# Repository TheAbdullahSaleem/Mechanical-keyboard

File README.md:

# Mechanical KEEB!!! 
This is a keyboard completely made by me 

## HOW THIS WAS MADE
I made it from scratch compltely scratch and followed the keeb.hackclub guide for it

## How to install:
It is not installable how ever you can see the 3d model at https://cad.onshape.com/documents/bb4cb905776d924b12e08e8f/w/9ffe8c12da04f62d852a73e0/e/dd87c740e253aa3d1df2d833?renderMode=0&uiState=6ac13d8ddb4687ee592e63fd
or just clone this repo

## FEEDBACK:
Your feedbacks are very valuable for us , message me on slack my handle is @Mewton (I know its funny it is like cat plus newton)

## AI DISCLOSURE
I used ai for some testing and clarity cuz it was my first project like this

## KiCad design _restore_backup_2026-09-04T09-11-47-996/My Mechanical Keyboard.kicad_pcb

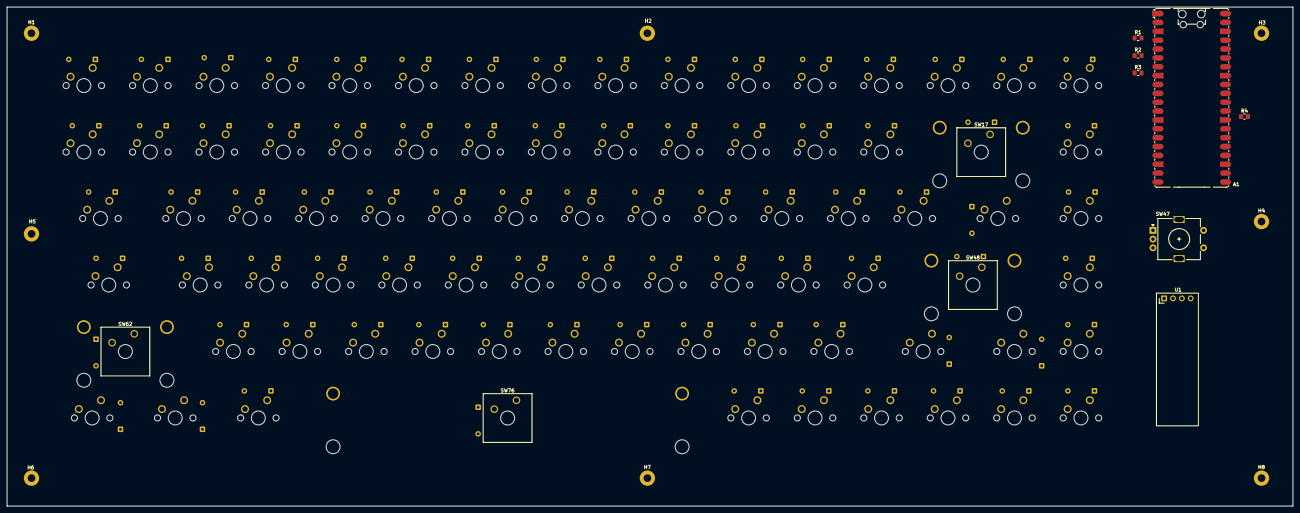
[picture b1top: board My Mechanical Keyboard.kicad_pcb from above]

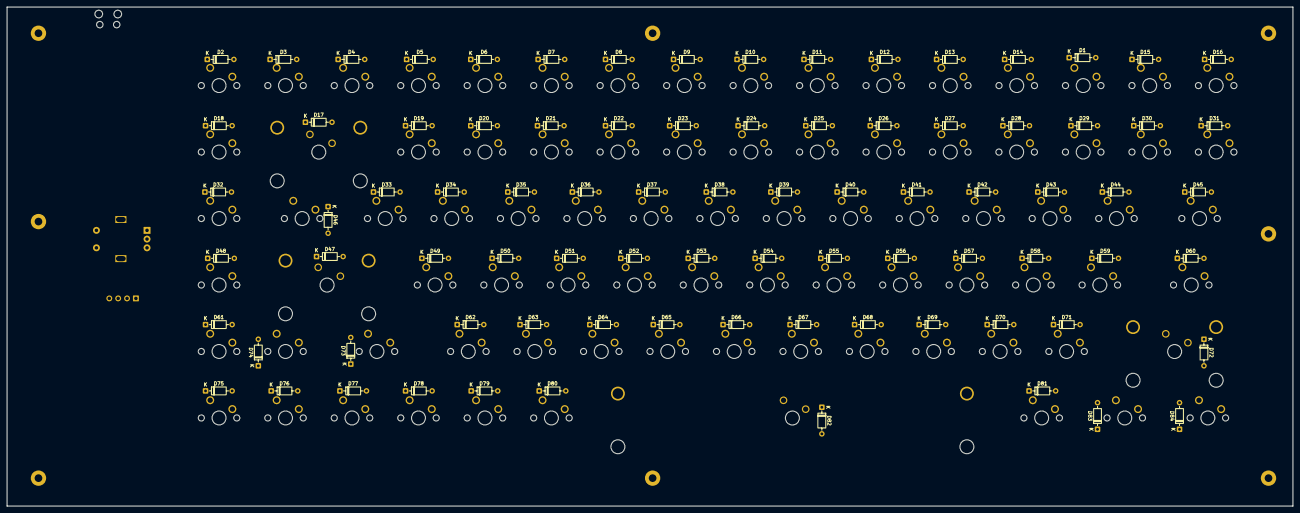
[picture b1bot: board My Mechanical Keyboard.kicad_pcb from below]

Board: 2 copper layers, 368.5 x 143.0 mm, 187 parts (84 on the bottom side), 111 nets, no tracks yet.

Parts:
A1: RaspberryPi_Pico; RaspberryPi_Pico_Common_SMD
D1, D2, D3, D4, D5, D6, D7, D8, D9, D10, D11, D12, D13, D14, D15, D16, D17, D18, D19, D20, D21, D22, D23, D24, D25, D26, D27, D28, D29, D30, D31, D32, D33, D34, D35, D36, D37, D38, D39, D40, D41, D42, D43, D44, D45, D46, D47, D48, D49, D50, D51, D52, D53, D54, D55, D56, D57, D58, D59, D60, D61, D62, D63, D64, D65, D66, D67, D68, D69, D70, D71, D72, D73, D74, D75, D76, D77, D78, D79, D80, D81, D82, D83, D84: 1N4148; D_DO-35_SOD27_P7.62mm_Horizontal
H1, H2, H3, H4, H5, H6, H7, H8: MountingHole; MountingHole_2.2mm_M2_Pad
R1, R2: 4.7k; R_0805_2012Metric_Pad1.20x1.40mm_HandSolder
R3, R4: 5.1k; R_0805_2012Metric_Pad1.20x1.40mm_HandSolder
S1: MX_stab; STAB_MX_P_2u
S2, S3: MX_stab; STAB_MX_P_2.25u
S4: MX_stab; STAB_MX_P_6.25u
SW1, SW2, SW3, SW4, SW5, SW6, SW7, SW8, SW9, SW10, SW11, SW12, SW13, SW14, SW15, SW16, SW18, SW19, SW20, SW21, SW22, SW23, SW24, SW25, SW26, SW27, SW28, SW29, SW30, SW31, SW33, SW34, SW35, SW36, SW37, SW38, SW39, SW40, SW41, SW42, SW43, SW44, SW46, SW50, SW51, SW52, SW53, SW54, SW55, SW56, SW57, SW58, SW59, SW60, SW61, SW63, SW64, SW65, SW66, SW67, SW68, SW69, SW70, SW71, SW72, SW74, SW75, SW80, SW81, SW82, SW83, SW84, SW85: SW_Push; SW_MX_1u
SW17: SW_Push; SW_Cherry_MX_2.00u_Plate
SW32, SW45: SW_Push; SW_MX_1.5u
SW47: RotaryEncoder_Switch; RotaryEncoder_Alps_EC11E-Switch_Vertical_H20mm
SW48, SW62: SW_Push; SW_Cherry_MX_2.25u_Plate
SW49, SW73: SW_Push; SW_MX_1.75u
SW76: SW_Push; SW_Cherry_MX_6.25u_Plate
SW77, SW78, SW79: SW_Push; SW_MX_1.25u
U1: ER_OLEDM0.91_1x-I2C

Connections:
+3V3: A1.36 (3V3), R1.2, R2.1, U1.2 (VCC)
/Col 1: A1.15 (GPIO11), SW1.1, SW18.1, SW32.1, SW49.1, SW62.1, SW77.1
/Col 2: A1.16 (GPIO12), SW2.1, SW19.1, SW33.1, SW50.1, SW63.1, SW78.1
/Col 3: A1.17 (GPIO13), SW3.1, SW20.1, SW34.1, SW51.1, SW64.1, SW79.1
/Col 4: A1.19 (GPIO14), SW4.1, SW21.1, SW35.1, SW52.1, SW65.1, SW76.1
/Col 5: A1.20 (GPIO15), SW5.1, SW22.1, SW36.1, SW53.1, SW66.1, SW67.1
/Col 6: A1.21 (GPIO16), SW6.1, SW23.1, SW37.1, SW54.1, SW55.1, SW68.1
/Col 7: A1.22 (GPIO17), SW7.1, SW24.1, SW38.1, SW39.1, SW56.1, SW69.1
/Col 8: A1.24 (GPIO18), SW8.1, SW25.1, SW26.1, SW40.1, SW57.1, SW70.1
/Col 9: A1.25 (GPIO19), SW9.1, SW27.1, SW41.1, SW58.1, SW71.1, SW80.1
/Col 10: A1.26 (GPIO20), SW10.1, SW28.1, SW42.1, SW59.1, SW72.1, SW81.1
/Col 11: A1.27 (GPIO21), SW11.1, SW29.1, SW43.1, SW60.1, SW73.1, SW82.1
/Col 12: A1.29 (GPIO22), SW12.1, SW30.1, SW44.1, SW48.1, SW74.1, SW83.1
/Col 13: A1.31 (GPIO26_ADC0), SW13.1, SW14.1, SW17.1, SW45.1, SW75.1, SW84.1
/Col 14: A1.32 (GPIO27_ADC1), SW15.1, SW16.1, SW31.1, SW46.1, SW61.1, SW85.1
/ENC_A: A1.1 (GPIO0), SW47.A
/ENC_B: A1.2 (GPIO1), SW47.B
/ENC_SW: A1.4 (GPIO2), SW47.S1
/Row 1: A1.7 (GPIO5), D1.2 (A), D3.2 (A), D5.2 (A), D6.2 (A), D7.2 (A), D8.2 (A), D9.2 (A), D10.2 (A), D11.2 (A), D12.2 (A), D13.2 (A), D14.2 (A), D15.2 (A), D16.2 (A)
/Row 2: A1.9 (GPIO6), D2.2 (A), D4.2 (A), D19.2 (A), D20.2 (A), D21.2 (A), D22.2 (A), D24.2 (A), D25.2 (A), D26.2 (A), D27.2 (A), D28.2 (A), D29.2 (A), D30.2 (A), D31.2 (A)
/Row 3: A1.10 (GPIO7), D17.2 (A), D18.2 (A), D23.2 (A), D33.2 (A), D34.2 (A), D35.2 (A), D36.2 (A), D39.2 (A), D40.2 (A), D41.2 (A), D42.2 (A), D43.2 (A), D44.2 (A), D45.2 (A)
/Row 4: A1.11 (GPIO8), D32.2 (A), D37.2 (A), D38.2 (A), D46.2 (A), D47.2 (A), D49.2 (A), D50.2 (A), D51.2 (A), D55.2 (A), D56.2 (A), D57.2 (A), D58.2 (A), D59.2 (A), D60.2 (A)
/Row 5: A1.12 (GPIO9), D48.2 (A), D52.2 (A), D53.2 (A), D54.2 (A), D61.2 (A), D62.2 (A), D63.2 (A), D68.2 (A), D69.2 (A), D70.2 (A), D71.2 (A), D72.2 (A), D73.2 (A), D74.2 (A)
/Row 6: A1.14 (GPIO10), D64.2 (A), D65.2 (A), D66.2 (A), D67.2 (A), D75.2 (A), D76.2 (A), D77.2 (A), D78.2 (A), D79.2 (A), D80.2 (A), D81.2 (A), D82.2 (A), D83.2 (A), D84.2 (A)
/SCL: A1.6 (GPIO4), R2.2, U1.3 (SCL)
/SDA: A1.5 (GPIO3), R1.1, U1.4 (SDA)
GND: A1.3 (GND), A1.8 (GND), A1.13 (GND), A1.18 (GND), A1.23 (GND), A1.28 (GND), A1.38 (GND), R3.1, R4.1, SW47.C, SW47.S2, U1.1 (GND)
unnamed: D16.1 (K), SW1.2
unnamed: D31.1 (K), SW18.2
unnamed: D45.1 (K), SW32.2
unnamed: D60.1 (K), SW49.2
unnamed: D72.1 (K), SW62.2
unnamed: D84.1 (K), SW77.2
unnamed: D15.1 (K), SW2.2
unnamed: D30.1 (K), SW19.2
unnamed: D44.1 (K), SW33.2
unnamed: D59.1 (K), SW50.2
unnamed: D71.1 (K), SW63.2
unnamed: D83.1 (K), SW78.2
unnamed: D1.1 (K), SW3.2
unnamed: D29.1 (K), SW20.2
unnamed: D43.1 (K), SW34.2
unnamed: D58.1 (K), SW51.2
unnamed: D70.1 (K), SW64.2
unnamed: D81.1 (K), SW79.2
unnamed: D14.1 (K), SW4.2
unnamed: D28.1 (K), SW21.2
unnamed: D42.1 (K), SW35.2
unnamed: D57.1 (K), SW52.2
unnamed: D69.1 (K), SW65.2
unnamed: D82.1 (K), SW76.2
unnamed: D13.1 (K), SW5.2
unnamed: D27.1 (K), SW22.2
unnamed: D41.1 (K), SW36.2
unnamed: D56.1 (K), SW53.2
unnamed: D68.1 (K), SW66.2
unnamed: D67.1 (K), SW67.2
unnamed: D12.1 (K), SW6.2
unnamed: D26.1 (K), SW23.2
unnamed: D40.1 (K), SW37.2
unnamed: D55.1 (K), SW54.2
unnamed: D54.1 (K), SW55.2
unnamed: D66.1 (K), SW68.2
unnamed: D11.1 (K), SW7.2
unnamed: D25.1 (K), SW24.2
unnamed: D39.1 (K), SW38.2
unnamed: D38.1 (K), SW39.2
unnamed: D53.1 (K), SW56.2
unnamed: D65.1 (K), SW69.2
unnamed: D10.1 (K), SW8.2
unnamed: D24.1 (K), SW25.2
unnamed: D23.1 (K), SW26.2
unnamed: D37.1 (K), SW40.2
unnamed: D52.1 (K), SW57.2
unnamed: D64.1 (K), SW70.2
unnamed: D9.1 (K), SW9.2
unnamed: D22.1 (K), SW27.2
unnamed: D36.1 (K), SW41.2
unnamed: D51.1 (K), SW58.2
unnamed: D63.1 (K), SW71.2
unnamed: D80.1 (K), SW80.2
unnamed: D8.1 (K), SW10.2
unnamed: D21.1 (K), SW28.2
unnamed: D35.1 (K), SW42.2
unnamed: D50.1 (K), SW59.2
unnamed: D62.1 (K), SW72.2
unnamed: D79.1 (K), SW81.2
unnamed: D7.1 (K), SW11.2
unnamed: D20.1 (K), SW29.2
unnamed: D34.1 (K), SW43.2
unnamed: D49.1 (K), SW60.2
unnamed: D73.1 (K), SW73.2
unnamed: D78.1 (K), SW82.2
unnamed: D6.1 (K), SW12.2
unnamed: D19.1 (K), SW30.2
unnamed: D33.1 (K), SW44.2
unnamed: D47.1 (K), SW48.2
unnamed: D74.1 (K), SW74.2
unnamed: D77.1 (K), SW83.2
unnamed: D5.1 (K), SW13.2
unnamed: D4.1 (K), SW14.2
unnamed: D17.1 (K), SW17.2
unnamed: D46.1 (K), SW45.2
unnamed: D61.1 (K), SW75.2
unnamed: D76.1 (K), SW84.2
unnamed: D3.1 (K), SW15.2
unnamed: D2.1 (K), SW16.2
unnamed: D18.1 (K), SW31.2
unnamed: D32.1 (K), SW46.2
unnamed: D48.1 (K), SW61.2
unnamed: D75.1 (K), SW85.2
